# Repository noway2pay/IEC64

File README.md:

# IEC64W - IEEE-488 Interface for Commodore C64 & C128

## Introduction

This is the replica of the IEC64 card from the 80's. It provides a GPIB (IEEE-488) connection and plugs into the expansion port of the Commodore C64 or C128.

Who the original developer of the card was, I could not find out. It was sold by "WAW Elektronik", "Jann Datentechnik" and "REX Datentechnik" in different versions, but the technical base and the kernal was always the same. With the Kernal only the switch-on message had been adapted according to the company.

This is the version that was sold by "WAW Elektronik" at that time.

# Technical

The card is based on Motorola's MC6821P Peripheral Interface Adapter. Furthermore the corresponding kernal file is directly integrated as EPROM on the card. 

So the card can be simply plugged into the computer and started immediately. The Kernal, as well as the whole card can be deactivated by DIP switch. The former is interesting if you want to run the Kernal internally in the computer.

The card can be set up in such a way that mixed operation of IEC, for example a 1541, and IEEE-488 is possible.

# BOM

The parts list is quite clear. You can get the MC6821P quite well via eBay or UTSource. Otherwise, I have named the brands as representatives. Comparison types of other manufacturers can also be taken.

| Quantity | Designator      | Manufacturer 1     | Manufacturer  Part Number 1 | Description                                                  |
| -------- | --------------- | ------------------ | --------------------------- | ------------------------------------------------------------ |
| 4        | C1,  C2, C3, C4 | Dersonic           | CC1H104ZA1PD3F5O3000        | Ceramic  Disc Capacitors 100nF -20%~+80% 50V Through Hole,P=2.54mm RoHS |
| 1        | J2              | L-Com              | CIB24SRA                    | L-COM  - CIB24SRA - CONNECTOR GPIB R/A FEMALE                |
| 2        | R1,  R2         | Yageo              | CFR-25JB-52-1K              | RES  1K OHM 1/4W 5% AXIAL                                    |
| 1        | RN2             | Vishay  Dale       | CSC06A0110K0GPA             | RES  ARRAY 5 RES 10K OHM 6SIP                                |
| 1        | RN1             | Vishay  Dale       | CSC05A0110K0GPA             | RES  ARRAY 4 RES 10K OHM 5SIP                                |
| 1        | (SW1  & SW2)    | Wurth  Electronics | 418117270906                | DIP  SWITCH 2.54MM PITCH 6POL 24V                            |
| 1        | U4              | Spansion           | AM27C128-150DC              | EPROM  UV 128K-Bit 16K x 8 150ns 28-Pin CDIP                 |
| 1        | U2              | Texas  Instruments | SN74LS11N                   | IC  GATE AND 3CH 3-INP 14DIP                                 |
| 1        | U1              | Texas  Instruments | SN74LS00N                   | IC,  74LS, 74LS00, DIP14, 5.25V                              |
| 1        | U3              | Motorola           | MC6821P                     | PERIPHERAL  INTERFACE ADAPTER (PIA)                          |

# PCB

The PCB can either be ordered directly from [PCBWay](https://www.pcbway.com/project/shareproject/IEC64W___IEEE_488_for_Commodore_C64___C128.html), or you can create it yourself from the Gerber files available here.

If you liked my project, I would be very happy about a small coffee donation.

# License

The contents of this repository, with the exception of the Docs and Software directories, are released under the following license:

- the "Creative Commons Attribution-NonCommercial-ShareAlike 4.0 International License" (CC BY-NC-SA 4.0) full text of this license is included in the [LICENSE.CC-NC-BY-SA-4.0](https://github.com/DL2DW/IEC64/blob/main/LICENSE.CC-NC-BY-SA) file and a copy can also be found at https://creativecommons.org/licenses/by-nc-sa/4.0/

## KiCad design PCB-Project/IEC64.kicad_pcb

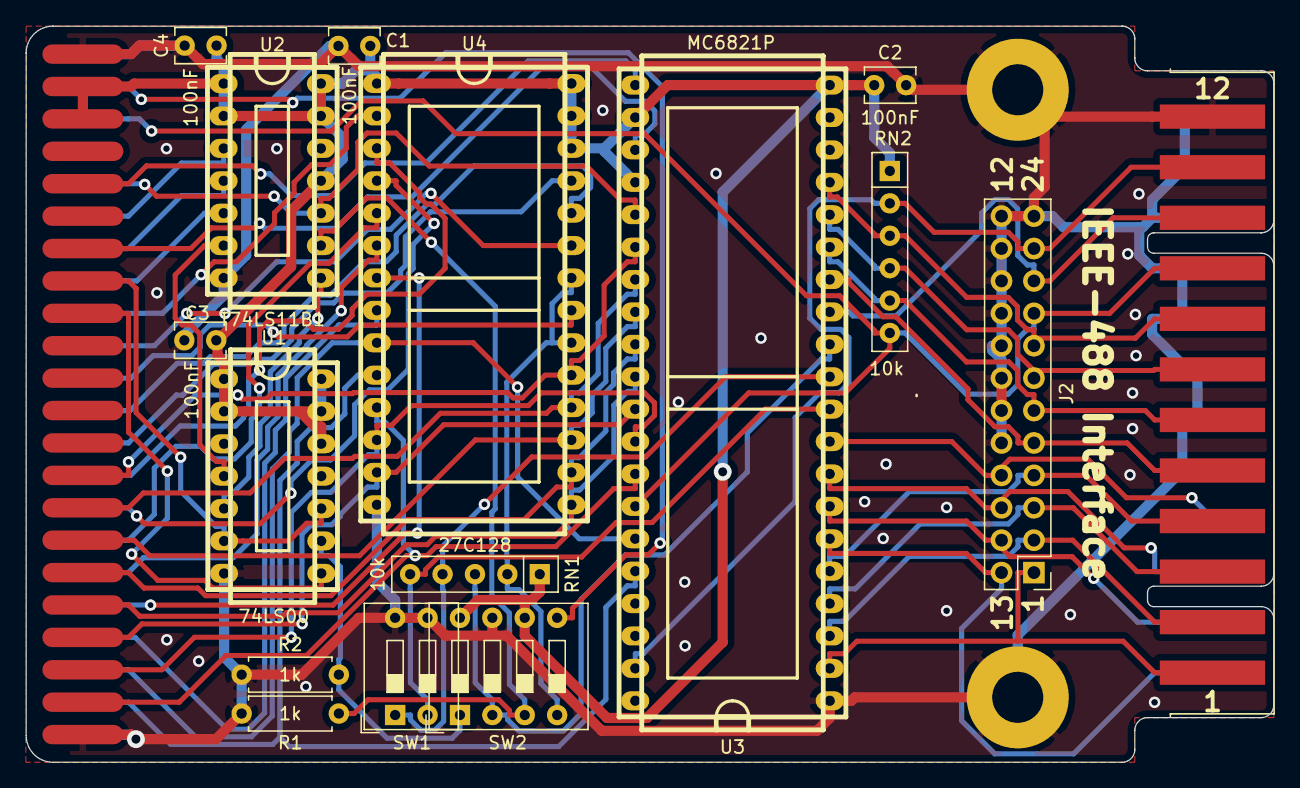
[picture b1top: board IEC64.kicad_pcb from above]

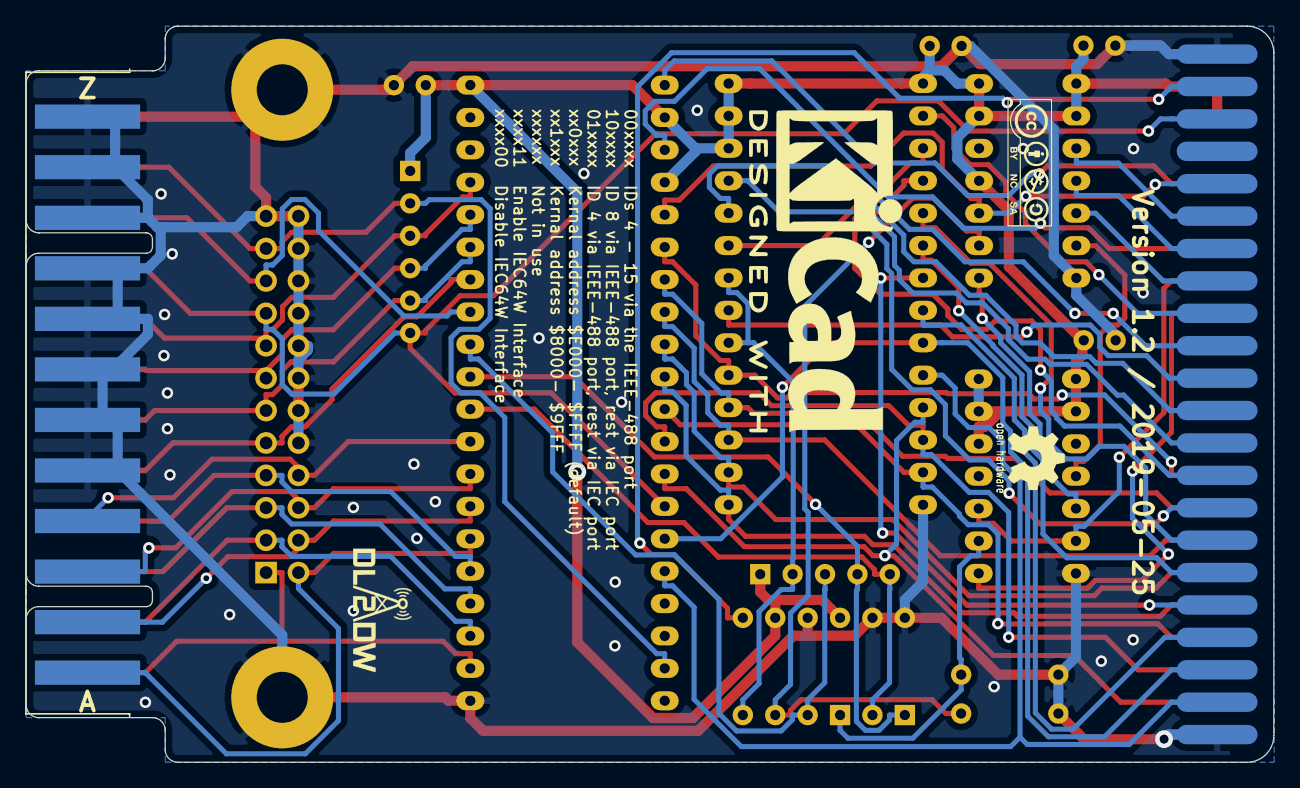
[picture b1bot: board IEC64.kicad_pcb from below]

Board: 2 copper layers, 97.8 x 57.7 mm, 23 parts (4 on the bottom side), 55 nets.

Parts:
C1, C2, C3, C4: 100nF; C_Disc_D3.8mm_W2.6mm_P2.50mm
CN1: IEEE-488 EDGE Connector; con-edge-156-MA12-2
J1: Expansion Connector; Expansion Port Edge Connector
J2: IEEE-488 Connector; PinHeader_2x12_P2.54mm_Top_Bottom_Vertical_Mirror
M1: SUNLOGO; KiCad-Logo2_12mm_SilkScreen
M2: SUNLOGO; DL2DW_Logo_Silk_10x5mm
M3: SUNLOGO; Logo_silk_CC-BY-NC-SA_10x3.6mm
M4: SUNLOGO; Logo_silk_OSHW_6x6mm
MH1, MH2: MountingHole_Pad; MountingHole_4mm_Pad
R1, R2: 1k; R_Axial_DIN0207_L6.3mm_D2.5mm_P7.62mm_Horizontal
RN1: 10k; R_Array_SIP5
RN2: 10k; R_Array_SIP6
SW1: SW_DIP_x02; SW_DIP_SPSTx02_Slide_9.78x7.26mm_W7.62mm_P2.54mm
SW2: SW_DIP_x04; SW_DIP_SPSTx04_Slide_9.78x12.34mm_W7.62mm_P2.54mm
U1: 74LS00; dil_14-300_socket
U2: T74LS11B1; dil_14-300_socket
U3: MC6821P; dil_40-600_socket
U4: 27C128; dil_28-600_socket

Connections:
+5V: C1.1, C2.1, C3.1, C4.1, J1.2, J1.3, RN1.1, RN2.1, SW2.6, SW2.8, U1.1, U1.2, U1.12, U1.13, U1.14, U2.1, U2.2, U2.11, U2.13, U2.14, U3.20, U3.22, U3.24, U4.1, U4.26, U4.27, U4.28
/A0: J1.Y, U3.36, U4.10
/A1: J1.X, U3.35, U4.9
/A2: J1.W, U4.8
/A3: J1.V, U4.7
/A4: J1.U, U4.6
/A5: J1.T, U4.5
/A6: J1.S, U4.4
/A7: J1.R, U4.3
/A8: J1.P, U4.25
/A9: J1.N, U4.24
/A10: J1.M, U4.21
/A11: J1.L, U4.23
/A12: J1.K, U4.2
/D0: J1.21, U3.33, U4.11
/D1: J1.20, U3.32, U4.12
/D2: J1.19, U3.31, U4.13
/D3: J1.18, U3.30, U4.15
/D4: J1.17, U3.29, U4.16
/D5: J1.16, U3.28, U4.17
/D6: J1.15, U3.27, U4.18
/D7: J1.14, U3.26, U4.19
/PHI2: J1.E, U2.10, U3.25
/R~W: J1.5, U3.21
/~ATN: CN1.11, J2.11, RN2.2, U3.39
/~DAV: CN1.6, J2.6, RN2.5, U3.15
/~DIO1: CN1.1, J2.1, U3.2
/~DIO2: CN1.2, J2.2, U3.3
/~DIO3: CN1.3, J2.3, U3.4
/~DIO4: CN1.4, J2.4, U3.5
/~DIO5: CN1.A, J2.13, U3.6
/~DIO6: CN1.B, J2.14, U3.7
/~DIO7: CN1.C, J2.15, U3.8
/~DIO8: CN1.D, J2.16, U3.9
/~EOI: CN1.5, J2.5, U3.14
/~EXROM: J1.9, U1.8
/~GAME: J1.8, U1.6, U1.10
/~IO1: J1.7, U3.23
/~NDAC: CN1.8, J2.8, RN2.3, U3.17
/~NRFD: CN1.7, J2.7, RN2.4, U3.16
/~ROMH: J1.B, SW2.5
/~SRQ: CN1.10, J2.10, U3.13
A13: J1.J, U2.5
A14: J1.H, U2.4
A15: J1.F, U2.3
GND: C1.2, C2.2, C3.2, C4.2, CN1.12, CN1.E, CN1.F, CN1.H, CN1.J, CN1.K, CN1.L, CN1.M, CN1.N, J1.1, J1.22, J1.A, J1.Z, J2.12, J2.17, J2.18, J2.19, J2.20, J2.21, J2.22, J2.23, J2.24, MH1.1, MH2.1, R1.1, R2.1, SW1.3, SW1.4, SW2.7, U1.7, U2.7, U3.1, U4.14
unnamed: R1.2, SW2.3, U2.9
unnamed: R2.2, SW2.1, U1.9
unnamed: RN1.2, SW2.4, U4.20, U4.22
unnamed: RN1.3, SW2.2, U3.12
unnamed: RN1.4, SW1.1, U3.11
unnamed: RN1.5, SW1.2, U3.10
unnamed: U1.4, U2.6
unnamed: U1.5, U2.8
~RESET: CN1.9, J1.C, J2.9, RN2.6, U3.34

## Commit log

2021-01-05 PCB order link added
